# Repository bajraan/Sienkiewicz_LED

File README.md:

# Sienkiewicz PCB

Sienkiewicz PCB project realized in KiCAD 9

> 🔗 Project main system repository: https://github.com/bajraan/Sienkiewicz__3ART00__SYSTEM

<h1 align="center">3ART13 LED</h1>

<p align="center" width="100%">
  
</p>

***

<p align="center">
  
&nbsp; &nbsp; &nbsp; &nbsp;
  
</p>

***

## SPECIFICATIONS

| Parameter | Value | 
| --- | --- |
| Dimensions | 38.0 × 38.0 mm |

***

## DIRECTORY STRUCTURE

    .
    ├─ Computations       # Misc calculations
    ├─ HTML               # HTML files for generated webpage
    ├─ Images             # Pictures and renders
    │
    ├─ kibot_resources    # External resources for KiBot
    │  ├─ colors          # Color theme for KiCad
    │  ├─ fonts           # Fonts used in the project
    │  ├─ scripts         # External scripts used with KiBot
    │  └─ templates       # Templates for KiBot generated reports
    │
    ├─ kibot_yaml         # KiBot YAML config files
    ├─ KiRI               # KiRI (PCB diff viewer) files
    │
    ├─ lib                # KiCad footprint and symbol libraries
    │  ├─ 3d_models       # Component 3D models
    │  ├─ lib_fp          # Footprint libraries
    │  └─ lib_sym         # Symbol libraries
    │
    ├─ Logos              # Logos
    │
    ├─ Manufacturing      # Assembly and fabrication documents
    │  ├─ Assembly        # Assembly documents (BoM, pos, notes)
    │  │
    │  └─ Fabrication     # Fabrication documents (ZIP, notes)
    │     ├─ Drill Tables # CSV drill tables
    │     └─ Gerbers      # Gerbers
    │
    ├─ Report             # Reports for ERC/DRC
    ├─ Schematic          # PDF of schematic
    ├─ Templates          # Title block templates
    ├─ Testing
    │  └─ Testpoints      # Testpoints tables      
    │
    └─ Variants           # Outputs for assembly variants

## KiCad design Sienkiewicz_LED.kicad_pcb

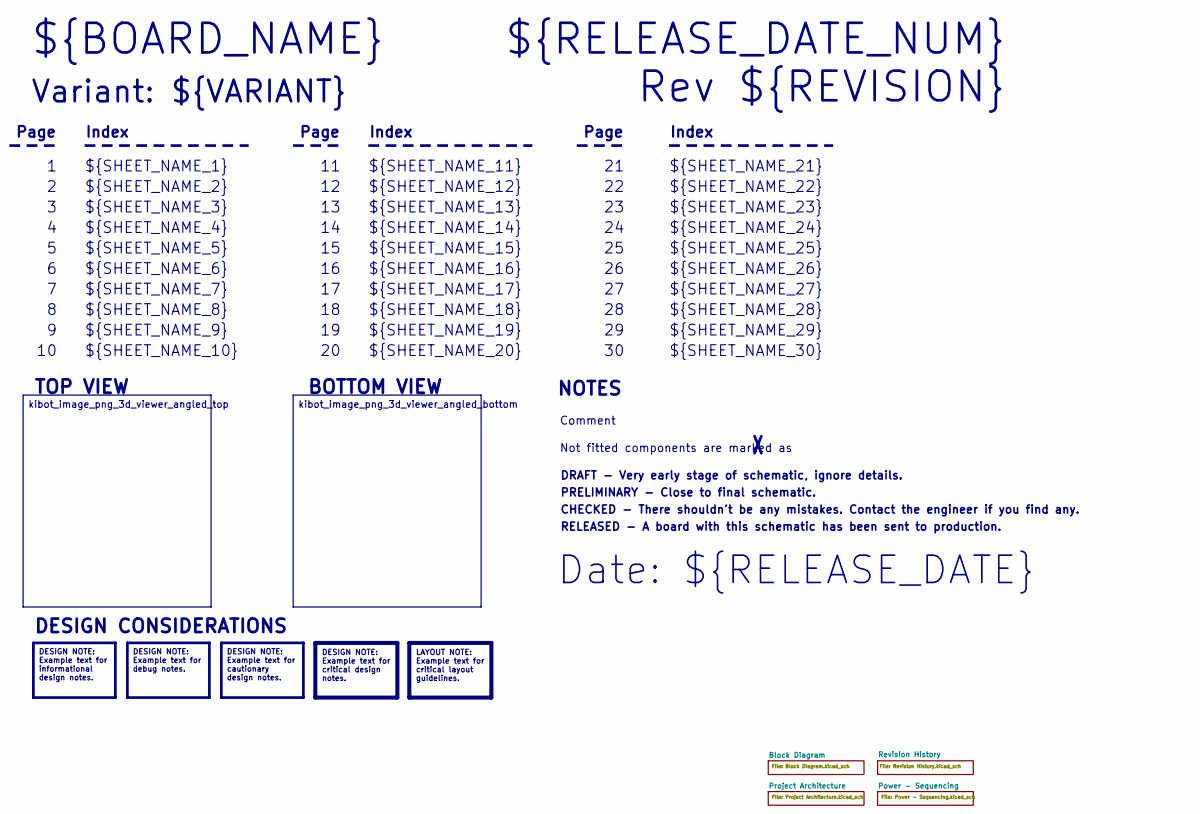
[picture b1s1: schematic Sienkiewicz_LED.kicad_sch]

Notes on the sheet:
Variant: ${VARIANT}
RELEASED - A board with this schematic has been sent to production.
${SHEET_NAME_24}
Index
PRELIMINARY - Close to final schematic.
${SHEET_NAME_22}
DRAFT - Very early stage of schematic, ignore details.
${SHEET_NAME_12}
${SHEET_NAME_8}
${SHEET_NAME_2}
${SHEET_NAME_5}
${SHEET_NAME_20}
Page
${SHEET_NAME_23}
${RELEASE_DATE_NUM}
Not fitted components are marked as
${SHEET_NAME_11}
${SHEET_NAME_6}
${SHEET_NAME_26}
Rev ${REVISION}
${SHEET_NAME_15}
CHECKED - There shouldn't be any mistakes. Contact the engineer if you find any.
BOTTOM VIEW
${SHEET_NAME_14}
${SHEET_NAME_21}
${SHEET_NAME_17}
${SHEET_NAME_18}
Date: ${RELEASE_DATE}
${SHEET_NAME_7}
${BOARD_NAME}
NOTES
${SHEET_NAME_1}
${SHEET_NAME_9}
${SHEET_NAME_29}
${SHEET_NAME_16}
${SHEET_NAME_3}
${SHEET_NAME_19}
Comment
TOP VIEW
${SHEET_NAME_10}

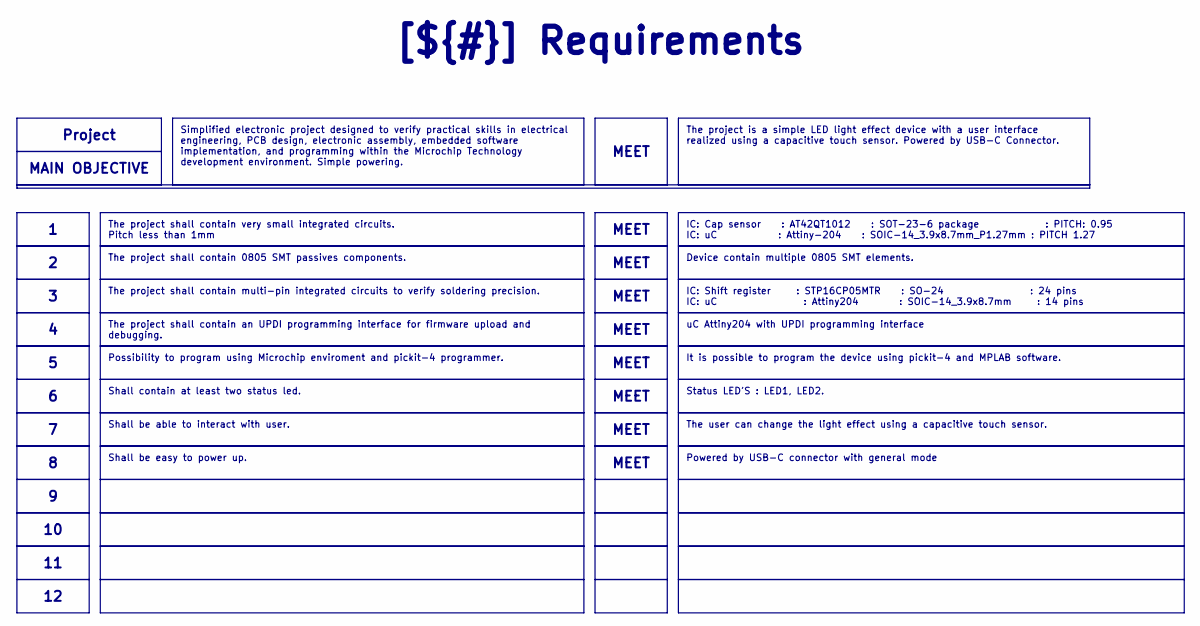
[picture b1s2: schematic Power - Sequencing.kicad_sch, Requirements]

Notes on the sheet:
Shall be able to interact with user.
IC: Cap sensor : AT42QT1012 : SOT-23-6 package : PITCH: 0.95 IC: uC : Attiny-204 : SOIC-14_3.9x8.7mm_P1.27mm : PITCH 1.27
Project
Shall be easy to power up.
Simplified electronic project designed to verify practical skills in electrical engineering, PCB design, electronic assembly, embedded software implementation, and programming within the Microchip Technology development environment. Simple powering.
MEET
Status LED'S : LED1, LED2.
uC Attiny204 with UPDI programming interface
The project shall contain 0805 SMT passives components.
Device contain multiple 0805 SMT elements.
The project shall contain very small integrated circuits. Pitch less than 1mm
[${#}] ${TITLE}
The project is a simple LED light effect device with a user interface realized using a capacitive touch sensor. Powered by USB-C Connector.
The user can change the light effect using a capacitive touch sensor.
IC: Shift register : STP16CP05MTR : SO-24 : 24 pins IC: uC : Attiny204 : SOIC-14_3.9x8.7mm : 14 pins
MAIN OBJECTIVE
Powered by USB-C connector with general mode
The project shall contain an UPDI programming interface for firmware upload and debugging.
Shall contain at least two status led.
It is possible to program the device using pickit-4 and MPLAB software.
Possibility to program using Microchip enviroment and pickit-4 programmer.
The project shall contain multi-pin integrated circuits to verify soldering precision.

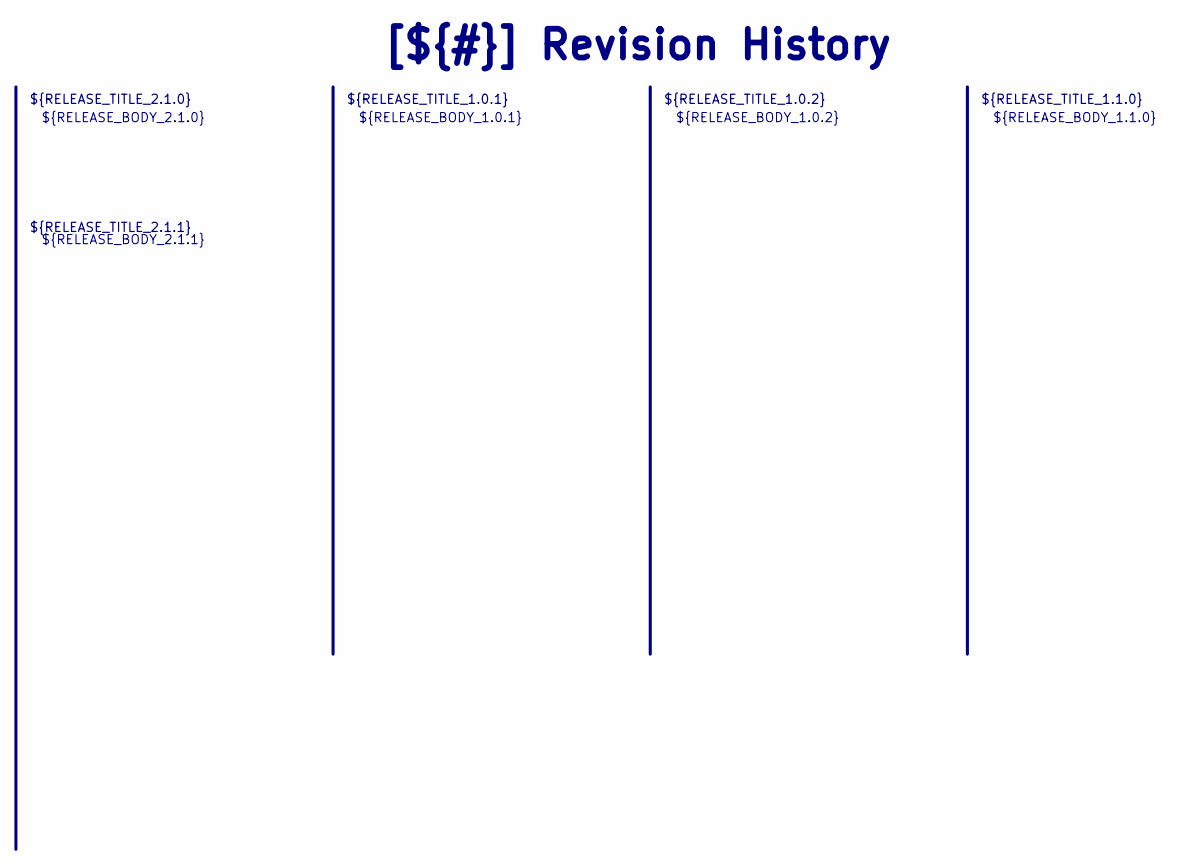
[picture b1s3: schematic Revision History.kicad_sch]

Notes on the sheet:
${RELEASE_TITLE_2.1.1}
${RELEASE_BODY_1.1.0}
[${#}] ${TITLE}
${RELEASE_BODY_2.1.0}
${RELEASE_TITLE_1.0.2}
${RELEASE_BODY_2.1.1}
${RELEASE_BODY_1.0.2}
${RELEASE_BODY_1.0.1}
${RELEASE_TITLE_2.1.0}
${RELEASE_TITLE_1.0.1}
${RELEASE_TITLE_1.1.0}

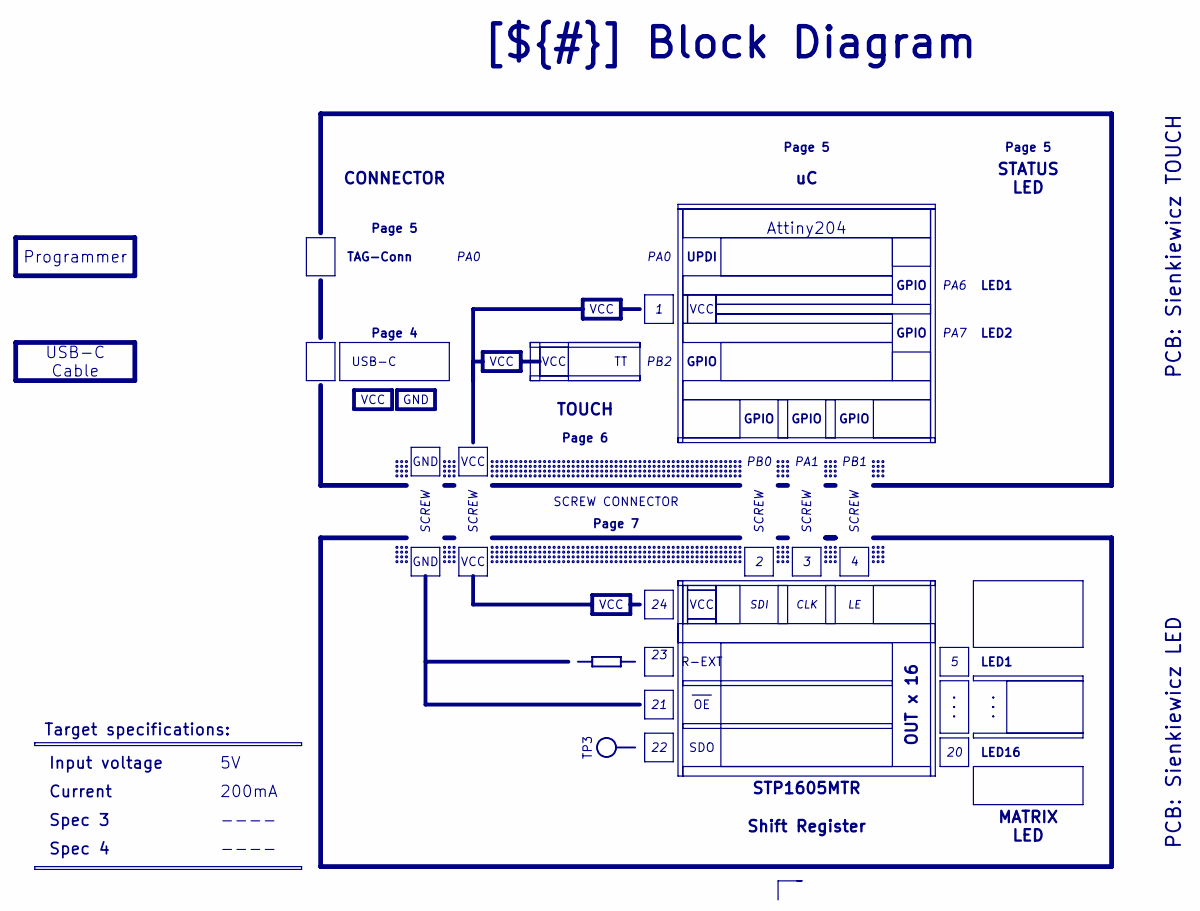
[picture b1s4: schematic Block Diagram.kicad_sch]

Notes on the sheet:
PCB: Sienkiewicz TOUCH
PCB: Sienkiewicz LED
MATRIX LED
VCC
LED1
Current
SDO
PB0
USB-C
GND
Input voltage
Page 5
PA1
TOUCH
CLK
PA7
200mA
SCREW
Spec 4
SDI
UPDI
SCREW CONNECTOR
PA6
Programmer
GPIO
Spec 3
Page 6
LED16
TP3
USB-C Cable
PA0
Page 7
Shift Register
STP1605MTR
Page 4
R-EXT
Attiny204
PB2
[${#}] ${TITLE}
OUT x 16

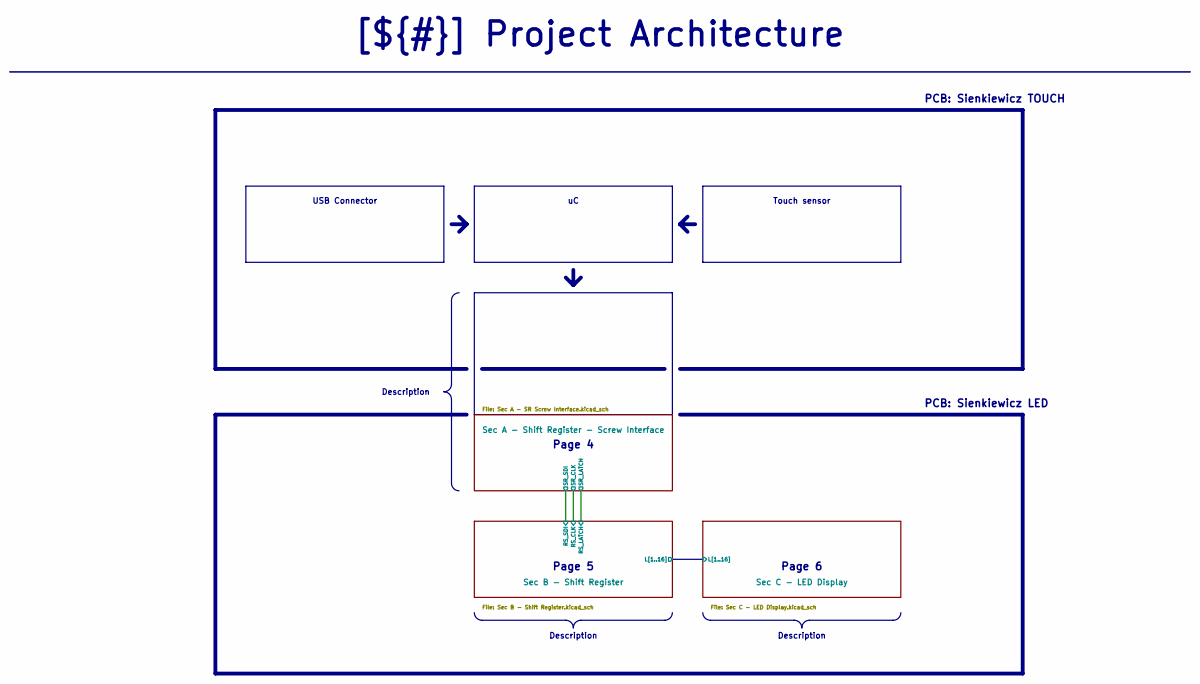
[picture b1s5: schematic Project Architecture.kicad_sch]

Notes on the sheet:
PCB: Sienkiewicz LED
Page 4
PCB: Sienkiewicz TOUCH
Touch sensor
USB Connector
Page 6
Page 5
Description
[${#}] ${TITLE}

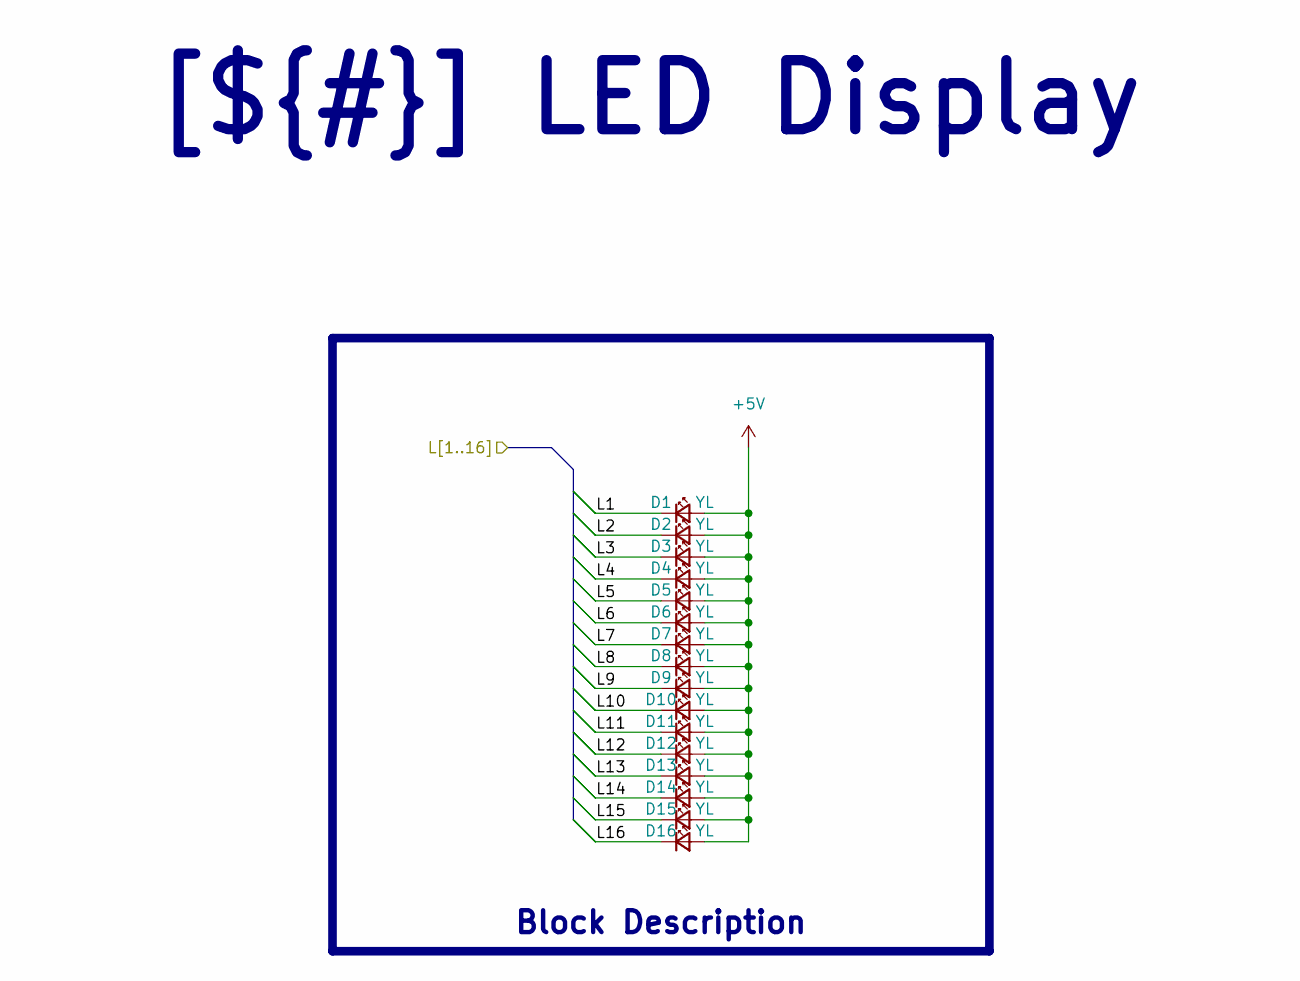
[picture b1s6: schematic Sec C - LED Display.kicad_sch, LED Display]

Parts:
D1, D2, D3, D4, D5, D6, D7, D8, D9, D10, D11, D12, D13, D14, D15, D16: YL; LED_1206_3216Metric

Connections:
+5V: D1.2 (A), D2.2 (A), D3.2 (A), D4.2 (A), D5.2 (A), D6.2 (A), D7.2 (A), D8.2 (A), D9.2 (A), D10.2 (A), D11.2 (A), D12.2 (A), D13.2 (A), D14.2 (A), D15.2 (A), D16.2 (A); also elsewhere on the board
/Project Architecture/Sec B - Shift Register/L1: D1.1 (K); also elsewhere on the board
/Project Architecture/Sec B - Shift Register/L2: D2.1 (K); also elsewhere on the board
/Project Architecture/Sec B - Shift Register/L3: D3.1 (K); also elsewhere on the board
/Project Architecture/Sec B - Shift Register/L4: D4.1 (K); also elsewhere on the board
/Project Architecture/Sec B - Shift Register/L5: D5.1 (K); also elsewhere on the board
/Project Architecture/Sec B - Shift Register/L6: D6.1 (K); also elsewhere on the board
/Project Architecture/Sec B - Shift Register/L7: D7.1 (K); also elsewhere on the board
/Project Architecture/Sec B - Shift Register/L8: D8.1 (K); also elsewhere on the board
/Project Architecture/Sec B - Shift Register/L9: D9.1 (K); also elsewhere on the board
/Project Architecture/Sec B - Shift Register/L10: D10.1 (K); also elsewhere on the board
/Project Architecture/Sec B - Shift Register/L11: D11.1 (K); also elsewhere on the board
/Project Architecture/Sec B - Shift Register/L12: D12.1 (K); also elsewhere on the board
/Project Architecture/Sec B - Shift Register/L13: D13.1 (K); also elsewhere on the board
/Project Architecture/Sec B - Shift Register/L14: D14.1 (K); also elsewhere on the board
/Project Architecture/Sec B - Shift Register/L15: D15.1 (K); also elsewhere on the board
/Project Architecture/Sec B - Shift Register/L16: D16.1 (K); also elsewhere on the board

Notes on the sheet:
[${#}] ${TITLE}
Block Description

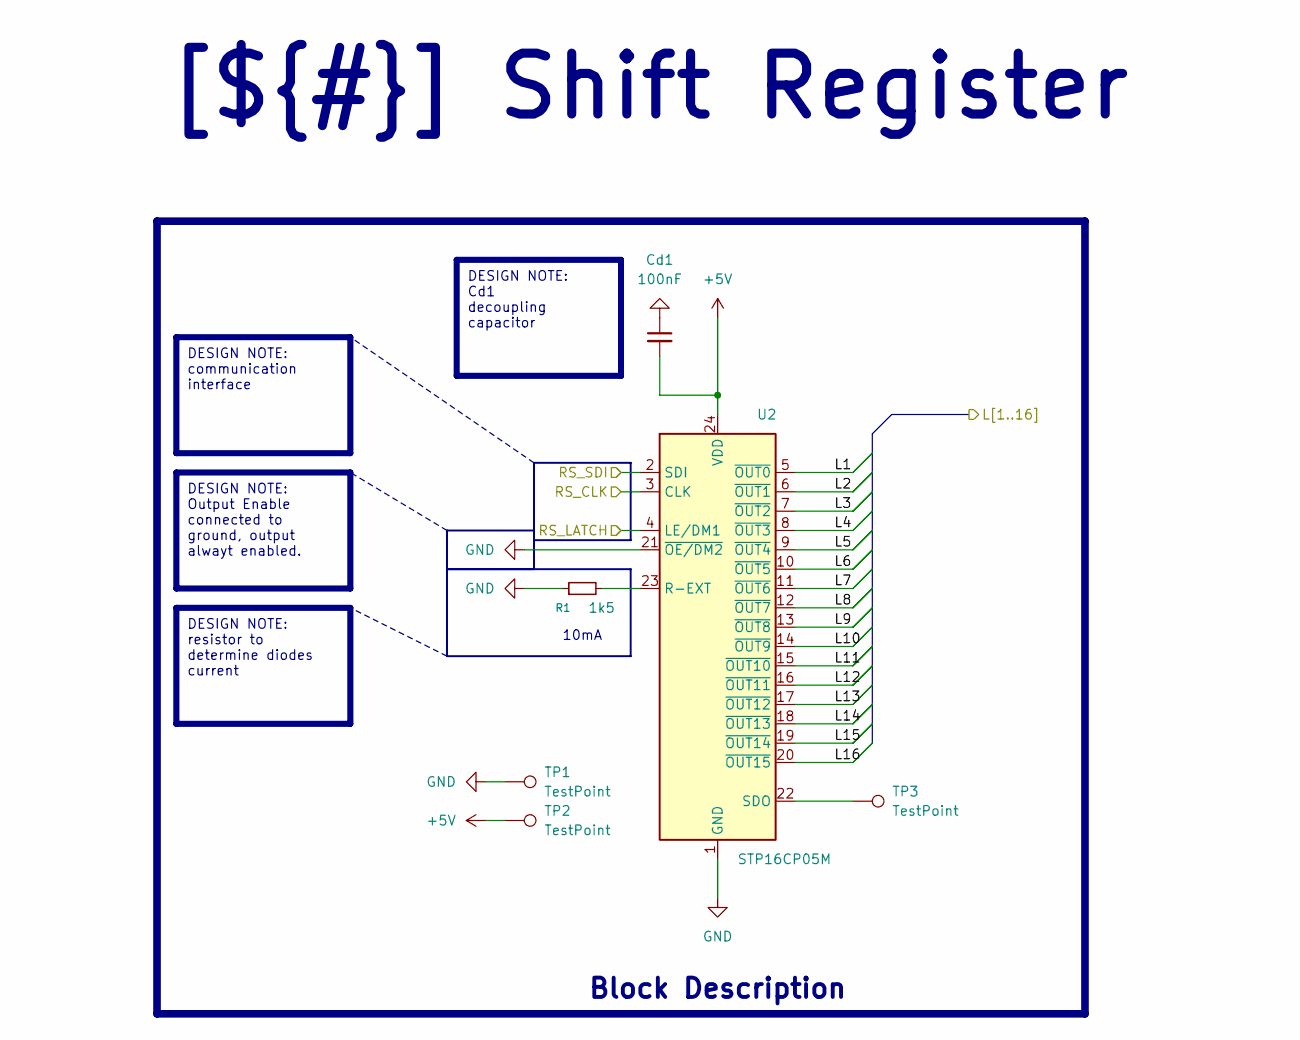
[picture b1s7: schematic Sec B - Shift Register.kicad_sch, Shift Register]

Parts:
Cd1: 100nF; C_1210_3225Metric
R1: 1k5; R_1206_3216Metric
TP1, TP2, TP3: TestPoint; TestPoint_Pad_D1.0mm
U2: STP16CP05M; SOIC-24W_7.5x15.4mm_P1.27mm

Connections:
+5V: Cd1.2, TP2.1, U2.24 (VDD); also elsewhere on the board
/Project Architecture/Sec A - Shift Register - Screw Interface/SR_CLK: U2.3 (CLK); also elsewhere on the board
/Project Architecture/Sec A - Shift Register - Screw Interface/SR_LATCH: U2.4 (LE/DM1); also elsewhere on the board
/Project Architecture/Sec A - Shift Register - Screw Interface/SR_SDI: U2.2 (SDI); also elsewhere on the board
/Project Architecture/Sec B - Shift Register/L1: U2.5 (~OUT0); also elsewhere on the board
/Project Architecture/Sec B - Shift Register/L2: U2.6 (~OUT1); also elsewhere on the board
/Project Architecture/Sec B - Shift Register/L3: U2.7 (~OUT2); also elsewhere on the board
/Project Architecture/Sec B - Shift Register/L4: U2.8 (~OUT3); also elsewhere on the board
/Project Architecture/Sec B - Shift Register/L5: U2.9 (~OUT4); also elsewhere on the board
/Project Architecture/Sec B - Shift Register/L6: U2.10 (~OUT5); also elsewhere on the board
/Project Architecture/Sec B - Shift Register/L7: U2.11 (~OUT6); also elsewhere on the board
/Project Architecture/Sec B - Shift Register/L8: U2.12 (~OUT7); also elsewhere on the board
/Project Architecture/Sec B - Shift Register/L9: U2.13 (~OUT8); also elsewhere on the board
/Project Architecture/Sec B - Shift Register/L10: U2.14 (~OUT9); also elsewhere on the board
/Project Architecture/Sec B - Shift Register/L11: U2.15 (~OUT10); also elsewhere on the board
/Project Architecture/Sec B - Shift Register/L12: U2.16 (~OUT11); also elsewhere on the board
/Project Architecture/Sec B - Shift Register/L13: U2.17 (~OUT12); also elsewhere on the board
/Project Architecture/Sec B - Shift Register/L14: U2.18 (~OUT13); also elsewhere on the board
/Project Architecture/Sec B - Shift Register/L15: U2.19 (~OUT14); also elsewhere on the board
/Project Architecture/Sec B - Shift Register/L16: U2.20 (~OUT15); also elsewhere on the board
GND: Cd1.1, R1.1, TP1.1, U2.1 (GND), U2.21 (~OE/DM2); also elsewhere on the board
unnamed: R1.2, U2.23 (R-EXT)
unnamed: TP3.1, U2.22 (SDO)

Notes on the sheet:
10mA
DESIGN NOTE: Output Enable connected to ground, output alwayt enabled.
[${#}] ${TITLE}
Block Description
DESIGN NOTE: Cd1 decoupling capacitor
DESIGN NOTE: communication interface
DESIGN NOTE: resistor to determine diodes current

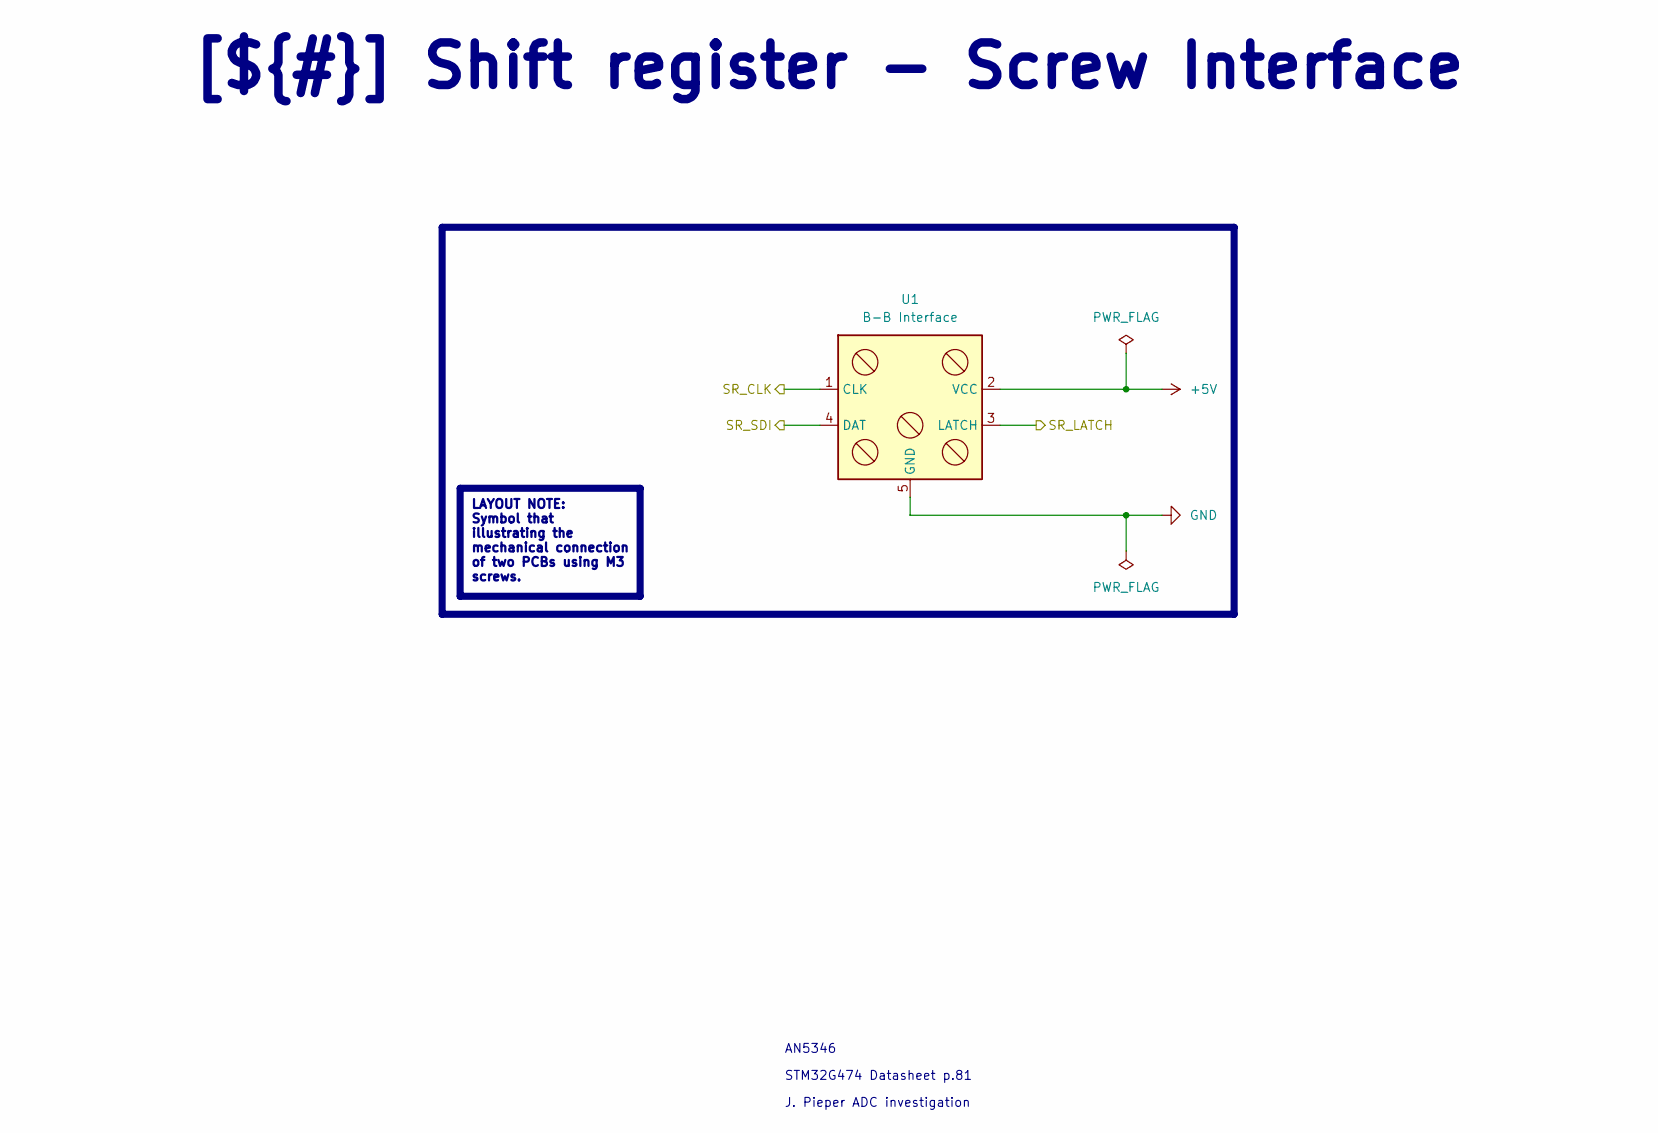
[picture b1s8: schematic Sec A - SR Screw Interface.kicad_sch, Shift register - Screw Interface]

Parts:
U1: B-B Interface; Sienkiewicz

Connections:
+5V: U1.2 (VCC); also elsewhere on the board
/Project Architecture/Sec A - Shift Register - Screw Interface/SR_CLK: U1.1 (CLK); also elsewhere on the board
/Project Architecture/Sec A - Shift Register - Screw Interface/SR_LATCH: U1.3 (LATCH); also elsewhere on the board
/Project Architecture/Sec A - Shift Register - Screw Interface/SR_SDI: U1.4 (DAT); also elsewhere on the board
GND: U1.5 (GND); also elsewhere on the board

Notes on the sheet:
J. Pieper ADC investigation
STM32G474 Datasheet p.81
AN5346
LAYOUT NOTE: Symbol that illustrating the mechanical connection of two PCBs using M3 screws.
[${#}] ${TITLE}

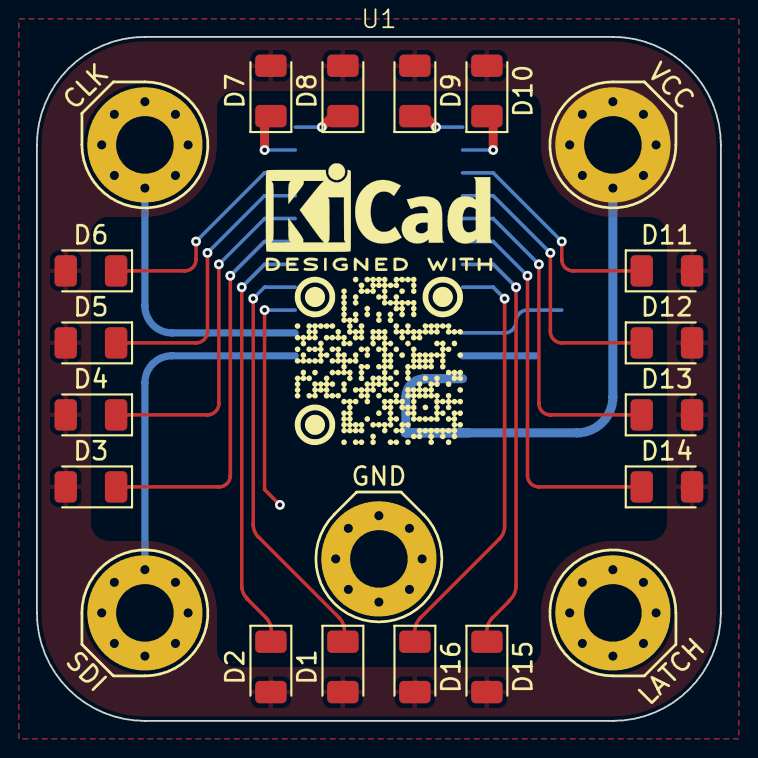
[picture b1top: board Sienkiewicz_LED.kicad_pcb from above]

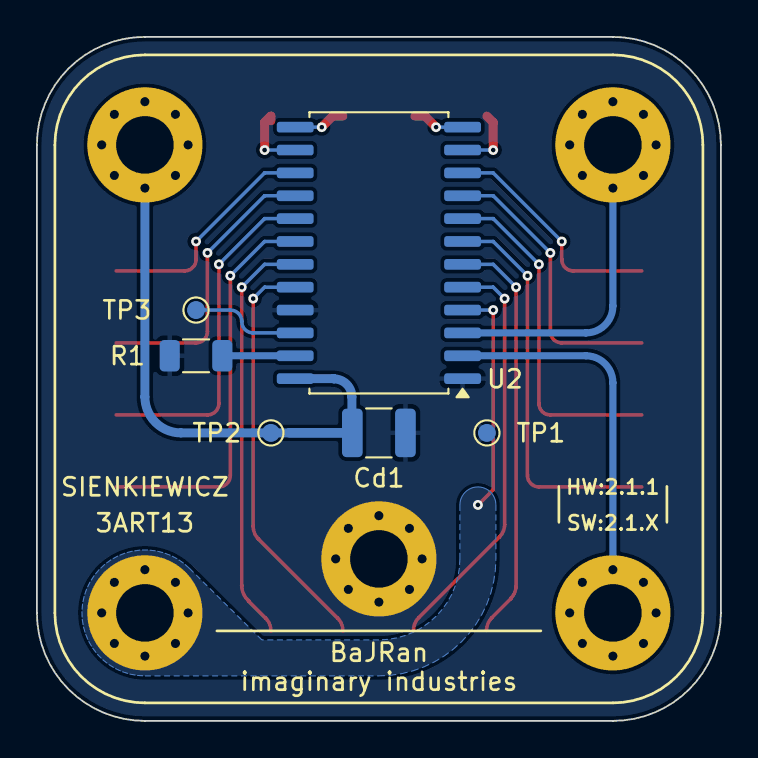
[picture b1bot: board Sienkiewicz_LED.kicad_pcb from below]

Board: 2 copper layers, 38.0 x 38.0 mm, 23 parts (6 on the bottom side), 23 nets.

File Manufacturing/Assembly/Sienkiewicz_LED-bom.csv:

Row,Quantity Per PCB,References,Value,Datasheet,Footprint,Description,Manufacturer,Manufacturer Part Number,Supplier Part Number
1,1,Cd1,100nF,~,C_1210_3225Metric,"Unpolarized capacitor, small symbol",,,
2,16,D1 D2 D3 D4 D5 D6 D7 D8 D9 D10 D11 D12 D13 D14 D15 D16,YL,~,LED_1206_3216Metric,"Light emitting diode, small symbol",,,
3,1,R1,1k5,~,R_1206_3216Metric,"Resistor, small symbol",,,
4,1,U1,B-B Interface,,Sienkiewicz,,,,
5,1,U2,STP16CP05M,https://www.st.com/resource/en/datasheet/stp16cp05.pdf,SOIC-24W_7.5x15.4mm_P1.27mm,"16-bit constant current LED sink driver, 5..100mA output current, 20V driving capability, 3.0..5.5V power supply, SOIC-24",,,

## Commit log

2026-04-30 Update Outputs
2026-04-30 [sch] first release of the schematic
2026-05-02 preliminary pcb version
2026-05-02 testpoints F.Fab descriptions removed
2026-05-02 F.Silkscreen update
2026-05-02 silkscreen test
2026-05-02 blender is wrongly rendering the images
2026-05-02 testpoints silkscreen tests
2026-05-02 blender rendering silkscreen solved
2026-05-02 checked version
2026-05-02 fix file
2026-05-02 Update CHANGELOG
2026-05-02 Update Outputs (release)
2026-05-21 documentation update / block diagram
2026-05-21 changed track to bus
2026-05-21 documentation update / release 2.1.1 prep
2026-05-21 2.1.1 release prep files
2026-05-21 block diagram update
2026-05-21 silkcreen version bump to 2.1.1
2026-05-21 pcb silkscreen version fix
2026-06-08 readme.md update
2026-06-08 readme update
2026-06-11 schematic update - block diagram pictures added
2026-06-11 fix naming CLK, SDI
